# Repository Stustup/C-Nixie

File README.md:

<# CNIX - Nixie Tube Clock ->WORK IN PROGRESS

CNIX is a nixie tube clock which accepts many diffrent nixie tubes with only slight modifications to the tube carrier board. 

The motivation was, that there are not many clocks out there that let you use almost any nixie tube you like. Most have fixed power supplies, 
underdesigned driver stages or inflexible microcontrollers. I hope to tackle these problems with an adjustable boost converter PSU, extremely 
flexible (and electrically protected) driver stages and an open source firmware written with free tools.

## Schematic

The control board consists of 3 parts:
- Power Supply
- Microcontroller
- I/O
- GPIO header for future ideas and feature expansion

Power comes from a simple USB-C plug configured for 5V 3A max with the 5k1 CC line resistors. I thought about adding a PD controller for higher input voltages,
but this would just have added complexity and locked you into more expensive USB PD power supplies.

The µC is a STM32G051, because it has an included RTC *with* added Vbat pin for an external battery, so that the RTC remembers time even when powered off. 
The unused GPIOs are broken out to a connector, so that in the future one could add cool stuff like a radio time reciever, a display or wifi.
Time is set manually with the push buttons on top. 

The PSU is heavily inspired by [this site](https://surfncircuits.com/2018/02/03/optimizing-the-5v-to-170v-nixie-tube-power-supply-design-part-2/). I highly advise you giving it a read. The article goes in depth with boost converter design and its challanges.

## Neat features

### Addon Boards
I designed an addon-board which just plugs into the broken out pins on the control board, to host all kinds of stuff. The one i already made has an DCF77 antenna for automatically getting the exact time OTA in germany. It also holds a HTU21 temperature and humidity sensor from TE, which can be accessed via a single press on the "menu" button on the control board. 
The addon-boards get detected via two pins (D2 a& D3), which form a 2 bit id system. so 0b11 means no board is connected, because i used internal pullups. the DCF77 board has the id 0b00, which deactivates the manual time setting menu and adds the temperature and humidity menu. 
With this all kinds of boards are possible, for example an ESP32 addon board with ESP-Home installed to integrate the clock and a sensor into homeassistant.

On the DCF77 Addon board there is a single pin to give structural strength to a simple perfboard on the main breakout bus. One can use this in tandem with the A1, A2, A3, A4, F0 and F1 pins.

![DCF77 Addon Board]

### Turn on/off timers
You can set power on and off times in the clock natively, so that the nixies dont always glow. With this the HT-power supply also gets deactivated to save power and lifespan of the parts. More advanced features like weekday dependant times have to be programmed directly into the µC, except if you want to code a big menu with just 3 buttons and 2 LEDs.

## TODO

- Change to new MCU. STM32H5 or ESP32. ESP32 for Wifi stuff like syncing time, Homeassistant integration etc. Could be done as module for the pinheader. STM32H5 for USBC pd
    - (DONE) Not necessary, BUT-> Create Plugin board for a DCF77 reciever conencting via GPIO
    - Addon board for Homeassistant Integration?
- (DONE) lower value caps for the LSE
- USB-PD (only with STM32H5) (Not neccessary)
- (DONE) HTU21 Temp and relative humidity sensor

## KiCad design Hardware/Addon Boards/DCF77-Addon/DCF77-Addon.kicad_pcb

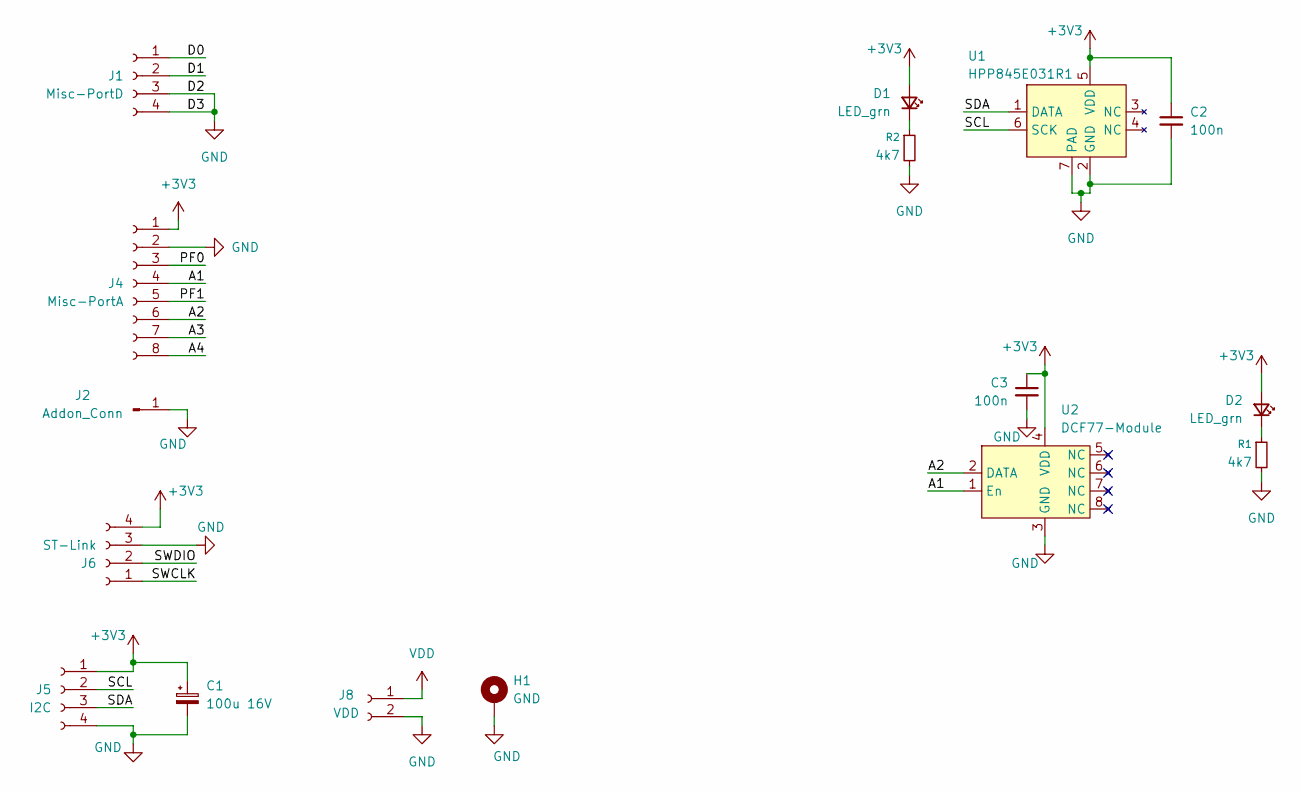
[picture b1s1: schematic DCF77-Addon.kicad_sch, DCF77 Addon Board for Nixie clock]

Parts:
C1: 100u 16V; CP_Elec_6.3x7.7
C2, C3: 100n; C_0805_2012Metric_Pad1.18x1.45mm_HandSolder
D1, D2: LED_grn; LED_0805_2012Metric_Pad1.15x1.40mm_HandSolder
H1: GND; TestPoint_Loop_D3.80mm_Drill2.0mm
J1: Misc-PortD; PinSocket_1x04_P2.54mm_Vertical
J2: Addon_Conn; PinHeader_1x01_P2.54mm_Vertical
J4: Misc-PortA; PinSocket_1x08_P2.54mm_Vertical
J5: I2C; PinSocket_1x04_P2.54mm_Vertical
J6: ST-Link; PinSocket_1x04_P2.54mm_Vertical
J8: VDD; PinSocket_1x02_P2.54mm_Vertical
R1, R2: 4k7; R_0805_2012Metric_Pad1.20x1.40mm_HandSolder
U1: HPP845E031R1; Maxim_TDFN-6-1EP_3x3mm_P0.95mm_EP1.5x2.3mm; Mouser Nr. 824-HPP845E031R1
U2: DCF77-Module

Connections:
+3V3: C1.1, C2.1, C3.1, D1.2 (A), D2.2 (A), J4.1, J5.1, J6.4, U1.5 (VDD), U2.4 (VDD)
/A1: J4.4, U2.1 (En)
/A2: J4.6, U2.2 (DATA)
/A3: J4.7
/A4: J4.8
/D0: J1.1
/D1: J1.2
/PF0: J4.3
/PF1: J4.5
/SCL: J5.2, U1.6 (SCK)
/SDA: J5.3, U1.1 (DATA)
/SWCLK: J6.1
/SWDIO: J6.2
GND: C1.2, C2.2, C3.2, H1.1, J1.3, J1.4, J2.1, J4.2, J5.4, J6.3, J8.2, R1.2, R2.2, U1.2 (GND), U1.7 (PAD), U2.3 (GND)
unnamed: D1.1 (K), R2.1
unnamed: D2.1 (K), R1.1
VDD: J8.1

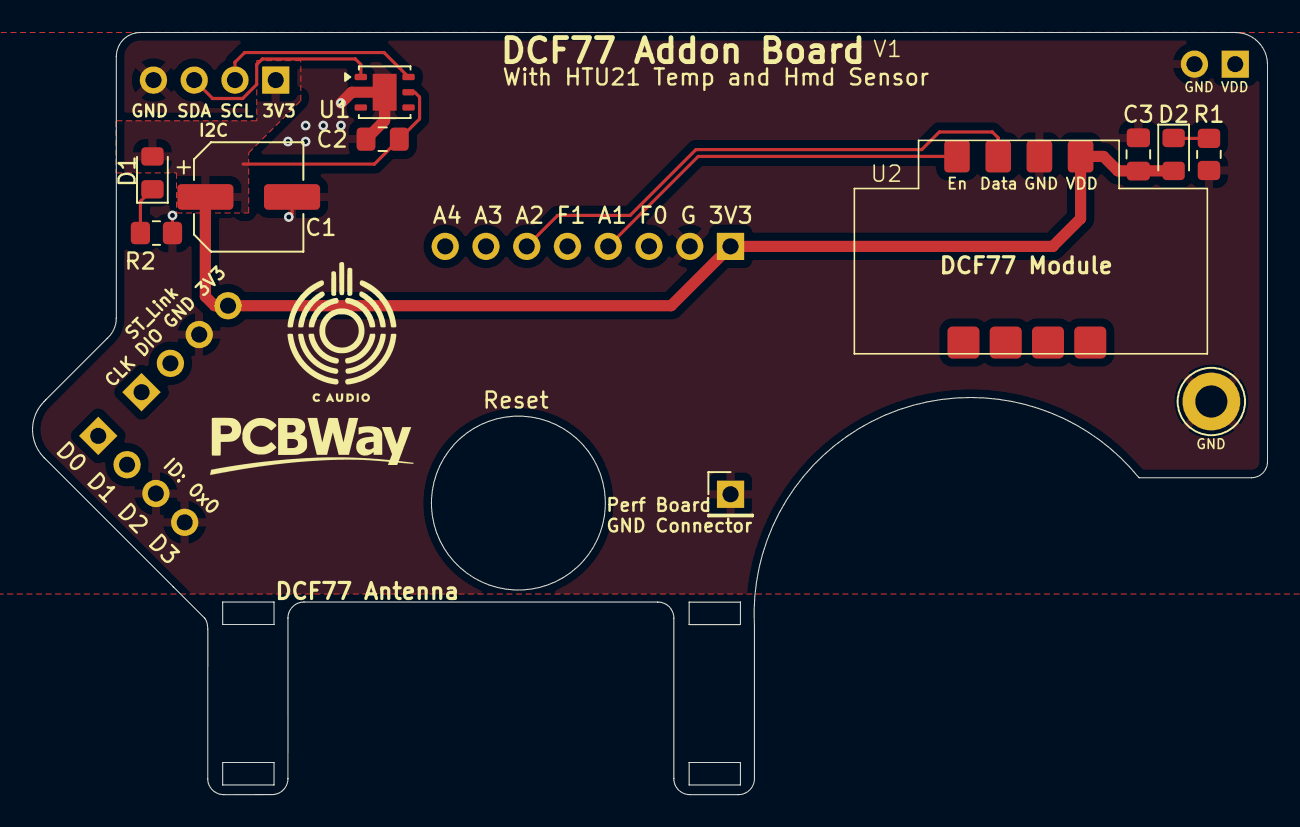
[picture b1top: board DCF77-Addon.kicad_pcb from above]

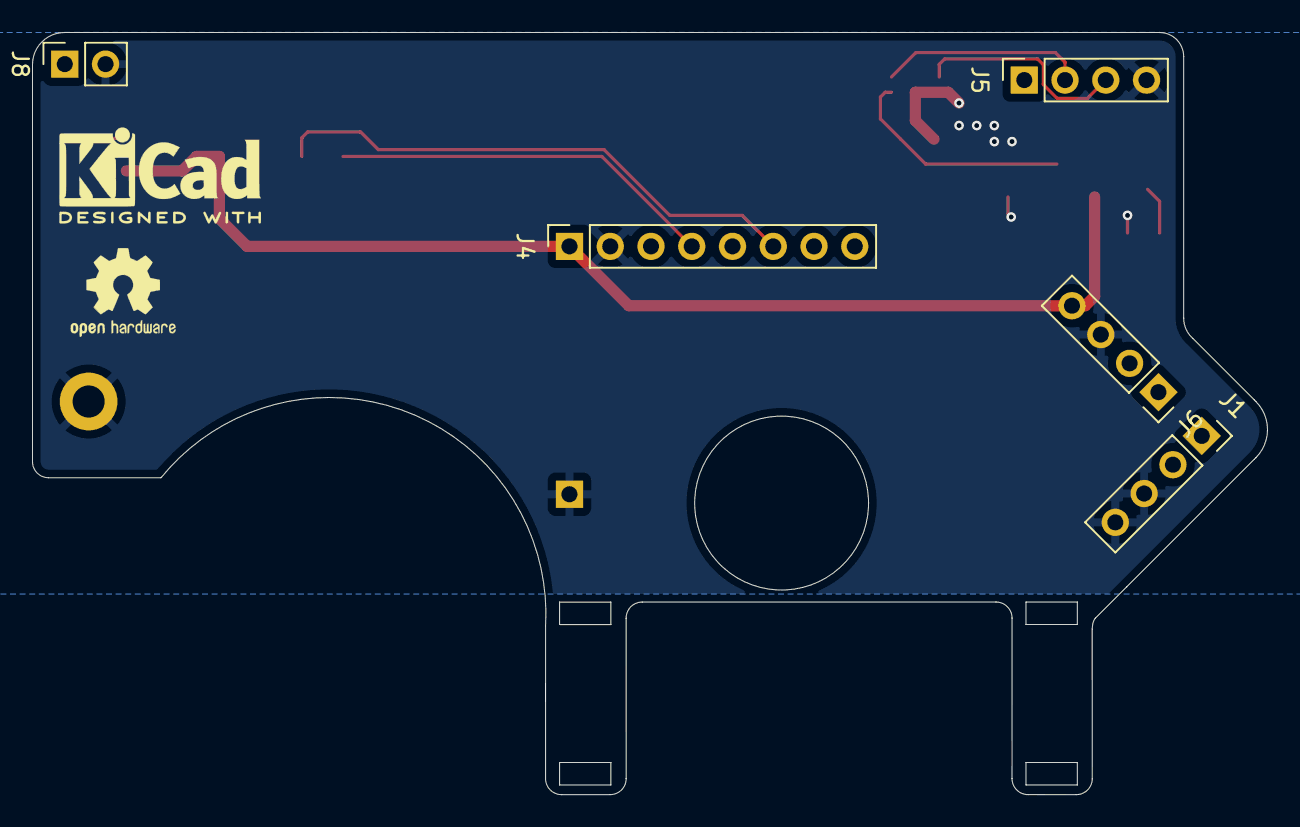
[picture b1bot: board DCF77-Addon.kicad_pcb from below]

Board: 2 copper layers, 77.0 x 47.5 mm, 16 parts (5 on the bottom side), 8 nets.

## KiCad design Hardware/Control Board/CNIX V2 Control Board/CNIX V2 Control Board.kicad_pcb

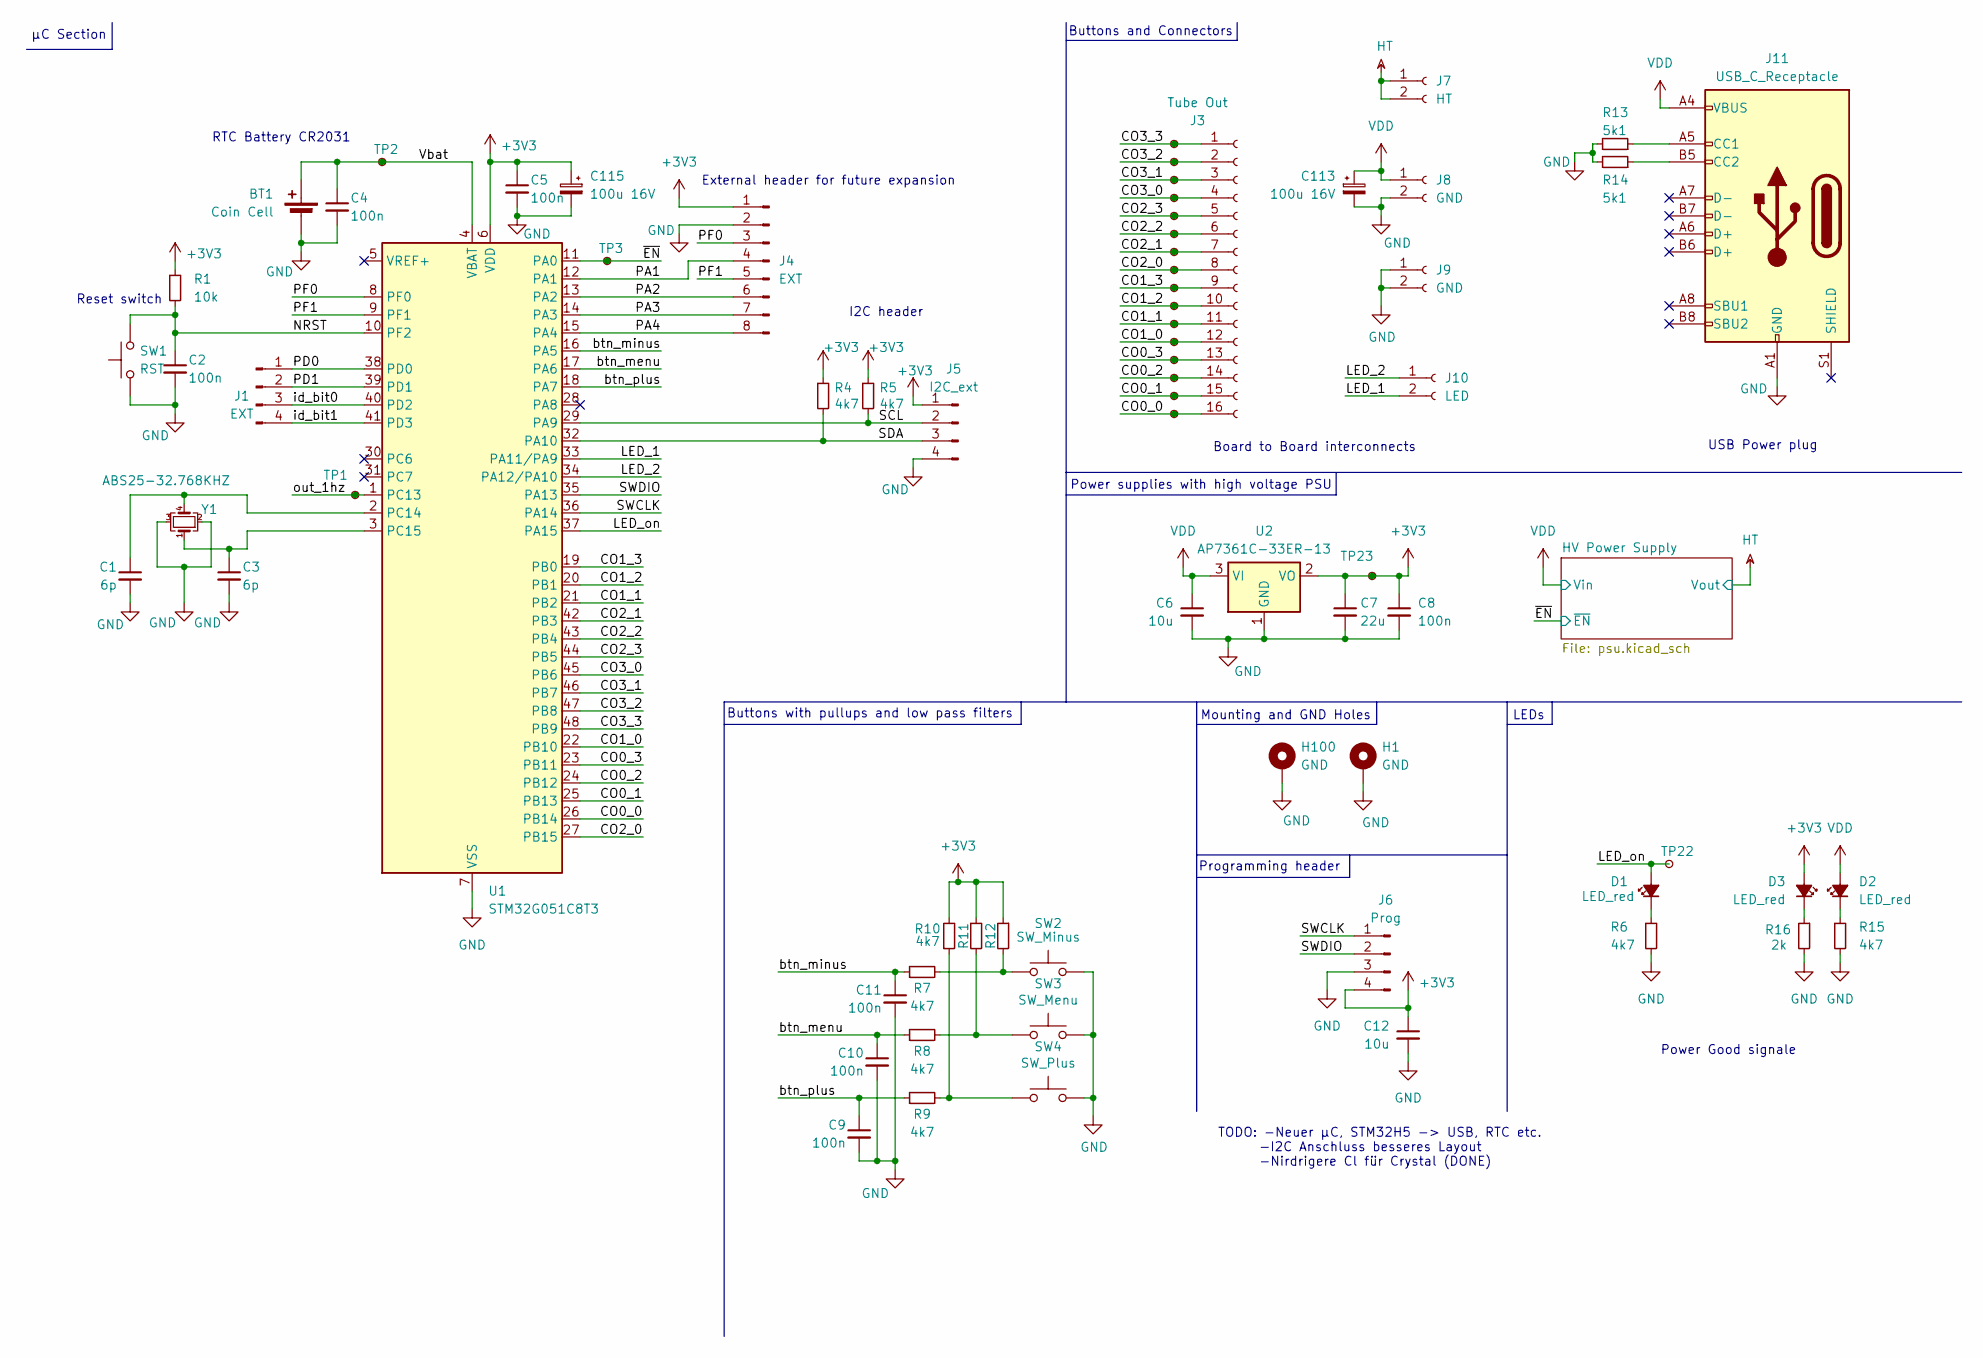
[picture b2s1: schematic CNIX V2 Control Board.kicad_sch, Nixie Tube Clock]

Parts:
BT1: Coin Cell; BatteryHolder_Renata_SMTU2032-LF_1x2032; Mouser Nr. 614-SMTU2032-LF.TR
C1, C3: 6p; C_0805_2012Metric_Pad1.18x1.45mm_HandSolder; Mouser Nr. 80-C0805C180K5HACTU
C2, C4, C5, C8, C9, C10, C11: 100n; C_0805_2012Metric_Pad1.18x1.45mm_HandSolder
C6, C12: 10u; C_0805_2012Metric_Pad1.18x1.45mm_HandSolder; Mouser Nr. 187-CL21B106KPQNNNE
C7: 22u; C_0805_2012Metric_Pad1.18x1.45mm_HandSolder; Mouser Nr. 187-CL21A226MQQNNNG
C113, C115: 100u 16V; CP_Elec_6.3x7.7; Mouser Nr. 710-865080343009
D1, D2, D3: LED_red; LED_0805_2012Metric_Pad1.15x1.40mm_HandSolder
H1: GND; TestPoint_Loop_D3.80mm_Drill2.0mm
H100: GND; TestPoint_Plated_Hole_D3.0mm
J1: EXT; PinHeader_1x04_P2.54mm_Vertical
J3: Tube Out; PinSocket_2x08_P2.54mm_Vertical
J4: EXT; PinHeader_1x08_P2.54mm_Vertical
J5: I2C_ext; PinHeader_1x04_P2.54mm_Vertical
J6: Prog; PinHeader_1x04_P2.54mm_Vertical
J7: HT; PinSocket_1x02_P2.54mm_Vertical
J8, J9: GND; PinSocket_1x02_P2.54mm_Vertical
J10: LED; PinSocket_1x02_P2.54mm_Vertical
J11: USB_C_Receptacle; USB_C_Receptacle_GCT_USB4085
R1: 10k; R_0805_2012Metric_Pad1.20x1.40mm_HandSolder
R4, R5, R6, R7, R8, R9, R10, R11, R12, R15: 4k7; R_0805_2012Metric_Pad1.20x1.40mm_HandSolder; Mouser Nr. 603-RC0805FR-074K7P
R13, R14: 5k1; R_0805_2012Metric_Pad1.20x1.40mm_HandSolder; Mouser Nr. 652-CR0805FX-5101ELF
R16: 2k; R_0805_2012Metric_Pad1.20x1.40mm_HandSolder; Mouser Nr. 603-RC0805FR-132KL
SW1: RST; SW_SPST_Omron_B3FS-100xP
SW2: SW_Minus; SW_Tactile_SPST_Angled_PTS645Vx31-2LFS
SW3: SW_Menu; SW_Tactile_SPST_Angled_PTS645Vx31-2LFS
SW4: SW_Plus; SW_Tactile_SPST_Angled_PTS645Vx31-2LFS
TP1, TP2, TP3, TP22, TP23: TestPoint_Small; TestPoint_Pad_D1.5mm
TP4, TP5, TP6, TP7, TP8, TP9, TP10, TP11, TP12, TP13, TP14, TP15, TP16, TP17, TP18, TP19: TestPoint_Small; TestPoint_THTPad_D1.0mm_Drill0.5mm
U1: STM32G051C8T3; LQFP-48_7x7mm_P0.5mm; Mouser Nr. 511-STM32G051C8T3
U2: AP7361C-33ER-13; SOT-223-3_TabPin2; Mouser-Nr. 621-AP7361C-33ER-13
Y1: ABS25-32.768KHZ; Crystal_SMD_Abracon_ABS25-4Pin_8.0x3.8mm; Mouser Nr. 815-ABS25-32.7-6-1-T

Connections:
+3V3: C5.1, C7.1, C8.1, C12.1, C115.1, D3.2 (A), J4.1, J5.1, J6.4, R1.1, R4.1, R5.1, R10.2, R11.1, R12.1, TP23.1, U1.6 (VDD), U2.2 (VO)
/CO0_0: J3.16, TP19.1, U1.26 (PB14)
/CO0_1: J3.15, TP18.1, U1.25 (PB13)
/CO0_2: J3.14, TP17.1, U1.24 (PB12)
/CO0_3: J3.13, TP16.1, U1.23 (PB11)
/CO1_0: J3.12, TP15.1, U1.22 (PB10)
/CO1_1: J3.11, TP14.1, U1.21 (PB2)
/CO1_2: J3.10, TP13.1, U1.20 (PB1)
/CO1_3: J3.9, TP12.1, U1.19 (PB0)
/CO2_0: J3.8, TP11.1, U1.27 (PB15)
/CO2_1: J3.7, TP10.1, U1.42 (PB3)
/CO2_2: J3.6, TP9.1, U1.43 (PB4)
/CO2_3: J3.5, TP8.1, U1.44 (PB5)
/CO3_0: J3.4, TP7.1, U1.45 (PB6)
/CO3_1: J3.3, TP6.1, U1.46 (PB7)
/CO3_2: J3.2, TP5.1, U1.47 (PB8)
/CO3_3: J3.1, TP4.1, U1.48 (PB9)
/LED_1: J10.2, U1.33 (PA11/PA9)
/LED_2: J10.1, U1.34 (PA12/PA10)
/LED_on: D1.2 (A), TP22.1, U1.37 (PA15)
/NRST: C2.1, R1.2, SW1.2, U1.10 (PF2)
/PA1: J4.4, U1.12 (PA1)
/PA2: J4.6, U1.13 (PA2)
/PA3: J4.7, U1.14 (PA3)
/PA4: J4.8, U1.15 (PA4)
/PD0: J1.1, U1.38 (PD0)
/PD1: J1.2, U1.39 (PD1)
/PF0: J4.3, U1.8 (PF0)
/PF1: J4.5, U1.9 (PF1)
/SCL: J5.2, R5.2, U1.29 (PA9)
/SDA: J5.3, R4.2, U1.32 (PA10)
/SWCLK: J6.1, U1.36 (PA14)
/SWDIO: J6.2, U1.35 (PA13)
/Vbat: BT1.1 (+), C4.1, TP2.1, U1.4 (VBAT)
/btn_menu: C10.1, R8.1, U1.17 (PA6)
/btn_minus: C11.1, R7.1, U1.16 (PA5)
/btn_plus: C9.1, R9.1, U1.18 (PA7)
/id_bit0: J1.3, U1.40 (PD2)
/id_bit1: J1.4, U1.41 (PD3)
/out_1hz: TP1.1, U1.1 (PC13)
/~EN: TP3.1, U1.11 (PA0); also elsewhere on the board
GND: BT1.2 (-), C1.2, C2.2, C3.2, C4.2, C5.2, C6.2, C7.2, C8.2, C9.2, C10.2, C11.2, C12.2, C113.2, C115.2, H1.1, H100.1, J4.2, J5.4, J6.3, J8.2, J9.1, J9.2, J11.A1 (GND), J11.A12 (GND), J11.B1 (GND), J11.B12 (GND), R6.2, R13.2, R14.2, R15.2, R16.2, SW1.1, SW2.2, SW3.2, SW4.2, U1.7 (VSS), U2.1 (GND), Y1.2, Y1.3; also elsewhere on the board
HT: J7.1, J7.2; also elsewhere on the board
unnamed: D1.1 (K), R6.1
unnamed: D2.1 (K), R15.1
unnamed: D3.1 (K), R16.1
unnamed: J11.A5 (CC1), R13.1
unnamed: J11.B5 (CC2), R14.1
unnamed: R9.2, R10.1, SW4.1
unnamed: R8.2, R11.2, SW3.1
unnamed: R7.2, R12.2, SW2.1
unnamed: C1.1, U1.2 (PC14), Y1.4
unnamed: C3.1, U1.3 (PC15), Y1.1
VDD: C6.1, C113.1, D2.2 (A), J8.1, J11.A4 (VBUS), J11.A9 (VBUS), J11.B4 (VBUS), J11.B9 (VBUS), U2.3 (VI); also elsewhere on the board

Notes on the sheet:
Board to Board interconnects
RTC Battery CR2031
µC Section
Programming header
External header for future expansion
Mounting and GND Holes
TODO: -Neuer µC, STM32H5 -> USB, RTC etc. -I2C Anschluss besseres Layout -Nirdrigere Cl für Crystal (DONE)
Power supplies with high voltage PSU
Buttons with pullups and low pass filters
Power Good signale
I2C header
USB Power plug
Reset switch
LEDs
Buttons and Connectors

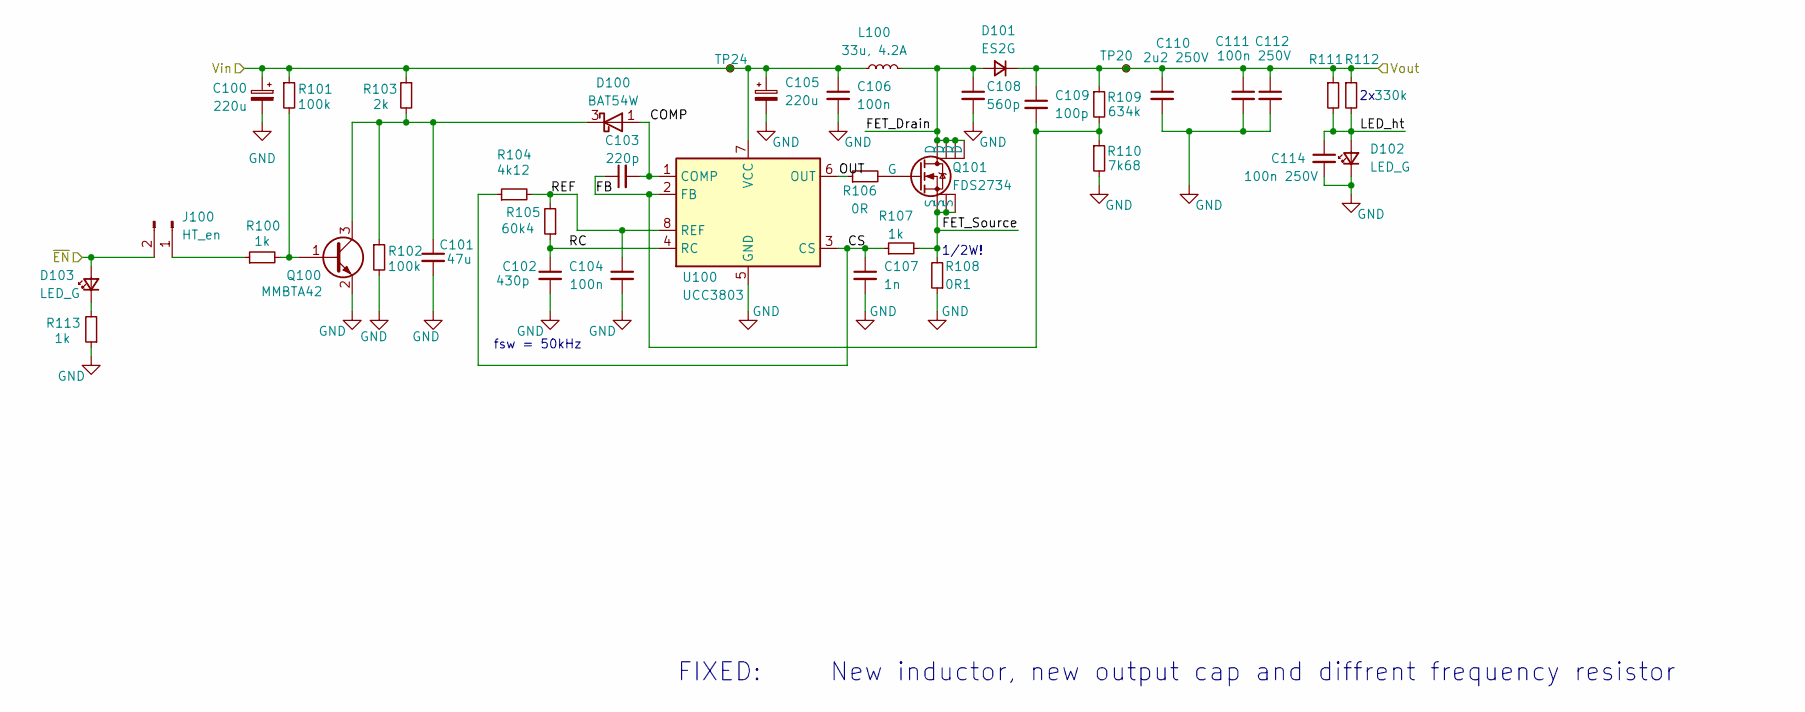
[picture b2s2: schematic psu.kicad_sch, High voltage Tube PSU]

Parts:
C100, C105: 220u; CP_Elec_8x10; Mouser Nr. 647-UUX1E221MNL6GS
C101: 47u; C_0805_2012Metric_Pad1.18x1.45mm_HandSolder; Mouser Nr. 187-CL21A476MRYNNNE
C102: 430p; C_0805_2012Metric_Pad1.18x1.45mm_HandSolder; Mouser Nr. 80-C0805C431J5G
C103: 220p; C_0805_2012Metric_Pad1.18x1.45mm_HandSolder; Mouser Nr. 710-885012207082
C104, C106: 100n; C_0805_2012Metric_Pad1.18x1.45mm_HandSolder
C107: 1n; C_0805_2012Metric_Pad1.18x1.45mm_HandSolder; Mouser Nr. 187-CL21B102KBANNNC
C108: 560p; C_0805_2012Metric_Pad1.18x1.45mm_HandSolder; Mouser Nr. 80-C0805C561K2R
C109: 100p; C_0805_2012Metric_Pad1.18x1.45mm_HandSolder; Mouser Nr. 581-08052C101K
C110: 2u2 250V; C_2220_5750Metric_Pad1.97x5.40mm_HandSolder; Mouser Nr. 710-885342214003
C111: 100nf 250V; C_0805_2012Metric_Pad1.18x1.45mm_HandSolder; Mouser Nr. 810-CGA4J3X7T2E104MA
C112, C114: 100n 250V; C_0805_2012Metric_Pad1.18x1.45mm_HandSolder; Mouser Nr. 810-CGA4J3X7T2E104MA
D100: BAT54W; SOT-323_SC-70; Mouser-Nr. 637-BAT54W
D101: ES2G; D_SMB_Handsoldering; Mouser Nr. 603-ES2G
D102, D103: LED_G; LED_0805_2012Metric
J100: HT_en; PinHeader_1x02_P2.54mm_Vertical
L100: 33u, 4.2A; L_12x12mm_H8mm; Mouser Nr. 7447709330
Q100: MMBTA42; SOT-23
Q101: FDS2734; SO-8_3.9x4.9mm_P1.27mm; Mouser Nr. 512-FDS2734
R100, R107, R113: 1k; R_0805_2012Metric_Pad1.20x1.40mm_HandSolder
R101, R102: 100k; R_0805_2012Metric_Pad1.20x1.40mm_HandSolder
R103: 2k; R_0805_2012Metric_Pad1.20x1.40mm_HandSolder; Mouser Nr. 603-RC0805FR-132KL
R104: 4k12; R_0805_2012Metric_Pad1.20x1.40mm_HandSolder; Mouser Nr. 603-RC0805FR-074K12L
R105: 60k4; R_0805_2012Metric_Pad1.20x1.40mm_HandSolder; Mouser Nr. 603-RE0805FRE0747KL
R106: 0R; R_0805_2012Metric_Pad1.20x1.40mm_HandSolder
R108: 0R1; R_1206_3216Metric_Pad1.30x1.75mm_HandSolder; Mouser Nr. 660-UR73VH2BTTDR100F
R109: 634k; R_1206_3216Metric_Pad1.30x1.75mm_HandSolder; Mouser Nr. 71-CRCW0805634KFKEA
R110: 7k68; R_1206_3216Metric_Pad1.30x1.75mm_HandSolder; Mouser Nr. 603-RC0805FR-077K68L
R111, R112: 330k; R_0805_2012Metric_Pad1.20x1.40mm_HandSolder; Mouser Nr. 603-AC0805FR-07330KL
TP20, TP24: TestPoint_Small; TestPoint_Pad_D1.5mm
U100: UCC3803; SOIC-8_3.9x4.9mm_P1.27mm; Mouser Nr. 595-UCC3803DTR

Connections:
/HV Power Supply/COMP: C103.2, D100.1 (A), U100.1 (COMP)
/HV Power Supply/CS: C107.1, R104.1, R107.1, U100.3 (CS)
/HV Power Supply/FB: C103.1, C109.2, R109.2, R110.1, U100.2 (FB)
/HV Power Supply/FET_Drain: C108.1, D101.2 (A), L100.2, Q101.5 (D), Q101.6 (D), Q101.7 (D), Q101.8 (D)
/HV Power Supply/FET_Source: Q101.1 (S), Q101.2 (S), Q101.3 (S), R107.2, R108.2
/HV Power Supply/LED_ht: C114.1, D102.2 (A), R111.2, R112.2
/HV Power Supply/OUT: R106.1, U100.6 (OUT)
/HV Power Supply/RC: C102.1, R105.1, U100.4 (RC)
/HV Power Supply/REF: C104.1, R104.2, R105.2, U100.8 (REF)
/~EN: D103.2 (A), J100.2; also elsewhere on the board
GND: C100.2, C101.2, C102.2, C104.2, C105.2, C106.2, C107.2, C108.2, C110.2, C111.2, C112.2, C114.2, D102.1 (K), Q100.2 (E), R102.2, R108.1, R110.2, R113.1, U100.5 (GND); also elsewhere on the board
HT: C109.1, C110.1, C111.1, C112.1, D101.1 (K), R109.1, R111.1, R112.1, TP20.1; also elsewhere on the board
unnamed: C101.1, D100.3 (K), Q100.3 (C), R102.1, R103.2
unnamed: D103.1 (K), R113.2
unnamed: J100.1, R100.1
unnamed: Q100.1 (B), R100.2, R101.2
unnamed: Q101.4 (G), R106.2
VDD: C100.1, C105.1, C106.1, L100.1, R101.1, R103.1, TP24.1, U100.7 (VCC); also elsewhere on the board

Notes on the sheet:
FIXED: New inductor, new output cap and diffrent frequency resistor
fsw = 50kHz
1/2W!

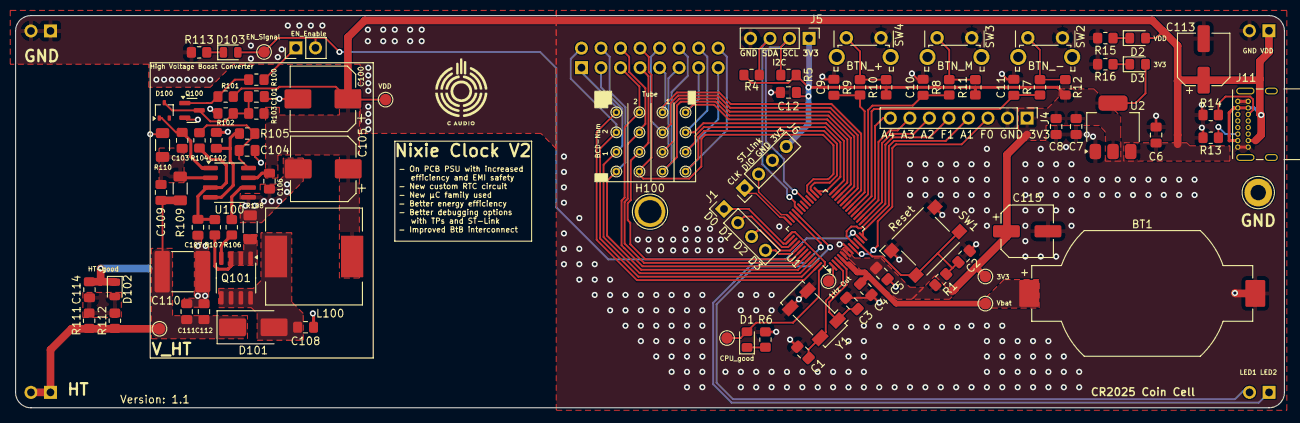
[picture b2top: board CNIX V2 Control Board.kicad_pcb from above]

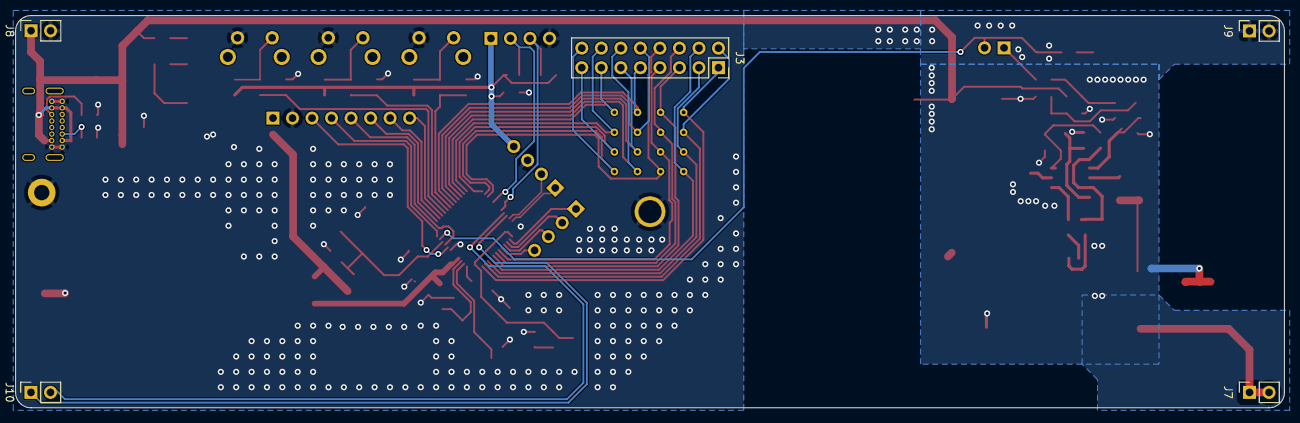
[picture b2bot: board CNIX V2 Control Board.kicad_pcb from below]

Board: 2 copper layers, 165.0 x 51.0 mm, 111 parts (5 on the bottom side), 68 nets.

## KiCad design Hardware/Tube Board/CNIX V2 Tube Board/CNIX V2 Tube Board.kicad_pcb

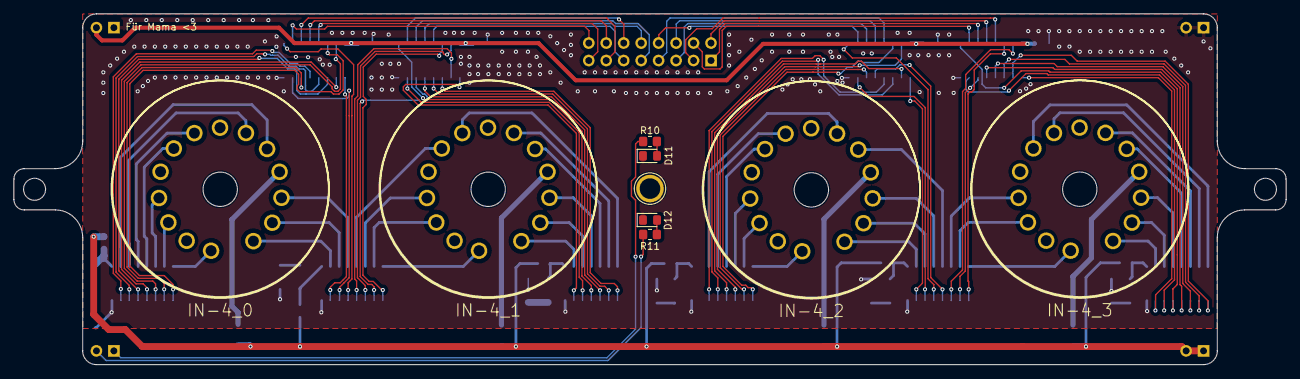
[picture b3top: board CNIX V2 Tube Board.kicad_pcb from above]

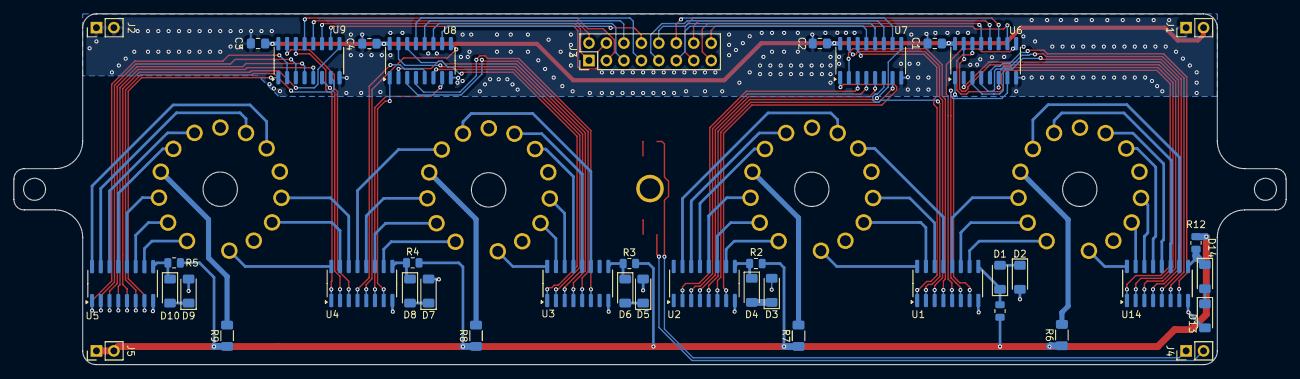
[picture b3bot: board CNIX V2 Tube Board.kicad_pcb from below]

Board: 2 copper layers, 185.0 x 51.0 mm, 50 parts (41 on the bottom side), 119 nets.

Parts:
C1, C2, C3, C4: 100n; C_0805_2012Metric_Pad1.18x1.45mm_HandSolder
D1, D2, D3, D4, D5, D6, D7, D8, D9, D10, D13, D14: TZMC47; D_MiniMELF
D11, D12: LED_Y; LED_0805_2012Metric_Pad1.15x1.40mm_HandSolder
H1: GND; TestPoint_Plated_Hole_D3.0mm
J1: VDD; PinHeader_1x02_P2.54mm_Vertical
J2: GND; PinHeader_1x02_P2.54mm_Vertical
J3: Tube Conn; PinHeader_2x08_P2.54mm_Vertical
J4: LED; PinHeader_1x02_P2.54mm_Vertical
J5: HT; PinHeader_1x02_P2.54mm_Vertical
R1, R2, R3, R4, R5, R12: 47k; R_0805_2012Metric
R6, R7, R8, R9: 18k7; R_1206_3216Metric_Pad1.30x1.75mm_HandSolder
R10, R11: 4k7; R_0805_2012Metric_Pad1.20x1.40mm_HandSolder
U1, U2, U3, U4, U5, U14: SN75468; SOIC-16_3.9x9.9mm_P1.27mm
U6, U7, U8, U9: 4028; SOIC-16_3.9x9.9mm_P1.27mm
U10: IN-4_0; IN-4
U11: IN-4_1; IN-4
U12: IN-4_2; IN-4
U13: IN-4_3; IN-4

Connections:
/CO0_0: J3.16, U6.10 (A)
/CO0_1: J3.15, U6.13 (B)
/CO0_2: J3.14, U6.12 (C)
/CO0_3: J3.13, U6.11 (D)
/CO1_0: J3.12, U7.10 (A)
/CO1_1: J3.11, U7.13 (B)
/CO1_2: J3.10, U7.12 (C)
/CO1_3: J3.9, U7.11 (D)
/CO2_0: J3.8, U8.10 (A)
/CO2_1: J3.7, U8.13 (B)
/CO2_2: J3.6, U8.12 (C)
/CO2_3: J3.5, U8.11 (D)
/CO3_0: J3.4, U9.10 (A)
/CO3_1: J3.3, U9.13 (B)
/CO3_2: J3.2, U9.12 (C)
/CO3_3: J3.1, U9.11 (D)
/LED1: J4.1, R10.1
/LED2: J4.2, R11.1
/T0_D0: U6.3 (S0), U14.5 (I5)
/T0_D1: U6.14 (S1), U14.1 (I1)
/T0_D2: U6.2 (S2), U14.4 (I4)
/T0_D3: U6.15 (S3), U14.3 (I3)
/T0_D4: U1.7 (I7), U6.1 (S4)
/T0_D5: U6.6 (S5), U14.2 (I2)
/T0_D6: U1.6 (I6), U6.7 (S6)
/T0_D7: U6.4 (S7), U14.6 (I6)
/T0_D8: U1.5 (I5), U6.9 (S8)
/T0_D9: U6.5 (S9), U14.7 (I7)
/T0_K0: U10.8 (K0), U14.12 (O5)
/T0_K1: U10.14 (K1), U14.16 (O1)
/T0_K2: U10.9 (K2), U14.13 (O4)
/T0_K3: U10.11 (K3), U14.14 (O3)
/T0_K4: U1.10 (O7), U10.1 (K4)
/T0_K5: U10.12 (K5), U14.15 (O2)
/T0_K6: U1.11 (O6), U10.2 (K6)
/T0_K7: U10.6 (K7), U14.11 (O6)
/T0_K8: U1.12 (O5), U10.3 (K8)
/T0_K9: U10.5 (K9), U14.10 (O7)
/T1_D0: U2.2 (I2), U7.3 (S0)
/T1_D1: U1.1 (I1), U7.14 (S1)
/T1_D2: U1.4 (I4), U7.2 (S2)
/T1_D3: U1.3 (I3), U7.15 (S3)
/T1_D4: U2.7 (I7), U7.1 (S4)
/T1_D5: U1.2 (I2), U7.6 (S5)
/T1_D6: U2.6 (I6), U7.7 (S6)
/T1_D7: U2.3 (I3), U7.4 (S7)
/T1_D8: U2.5 (I5), U7.9 (S8)
/T1_D9: U2.4 (I4), U7.5 (S9)
/T1_K0: U2.15 (O2), U11.8 (K0)
/T1_K1: U1.16 (O1), U11.14 (K1)
/T1_K2: U1.13 (O4), U11.9 (K2)
/T1_K3: U1.14 (O3), U11.11 (K3)
/T1_K4: U2.10 (O7), U11.1 (K4)
/T1_K5: U1.15 (O2), U11.12 (K5)
/T1_K6: U2.11 (O6), U11.2 (K6)
/T1_K7: U2.14 (O3), U11.6 (K7)
/T1_K8: U2.12 (O5), U11.3 (K8)
/T1_K9: U2.13 (O4), U11.5 (K9)
/T2_D0: U3.5 (I5), U8.3 (S0)
/T2_D1: U3.1 (I1), U8.14 (S1)
/T2_D2: U3.4 (I4), U8.2 (S2)
/T2_D3: U3.3 (I3), U8.15 (S3)
/T2_D4: U4.7 (I7), U8.1 (S4)
/T2_D5: U3.2 (I2), U8.6 (S5)
/T2_D6: U4.6 (I6), U8.7 (S6)
/T2_D7: U3.6 (I6), U8.4 (S7)
/T2_D8: U4.5 (I5), U8.9 (S8)
/T2_D9: U4.4 (I4), U8.5 (S9)
/T2_K0: U3.12 (O5), U12.8 (K0)
/T2_K1: U3.16 (O1), U12.14 (K1)
/T2_K2: U3.13 (O4), U12.9 (K2)
/T2_K3: U3.14 (O3), U12.11 (K3)
/T2_K4: U4.10 (O7), U12.1 (K4)
/T2_K5: U3.15 (O2), U12.12 (K5)
/T2_K6: U4.11 (O6), U12.2 (K6)
/T2_K7: U3.11 (O6), U12.6 (K7)
/T2_K8: U4.12 (O5), U12.3 (K8)
/T2_K9: U4.13 (O4), U12.5 (K9)
/T3_D0: U5.2 (I2), U9.3 (S0)
/T3_D1: U4.1 (I1), U9.14 (S1)
/T3_D2: U5.1 (I1), U9.2 (S2)
/T3_D3: U4.3 (I3), U9.15 (S3)
/T3_D4: U5.7 (I7), U9.1 (S4)
/T3_D5: U4.2 (I2), U9.6 (S5)
/T3_D6: U5.6 (I6), U9.7 (S6)
/T3_D7: U5.3 (I3), U9.4 (S7)
/T3_D8: U5.5 (I5), U9.9 (S8)
/T3_D9: U5.4 (I4), U9.5 (S9)
/T3_K0: U5.15 (O2), U13.8 (K0)
/T3_K1: U4.16 (O1), U13.14 (K1)
/T3_K2: U5.16 (O1), U13.9 (K2)
/T3_K3: U4.14 (O3), U13.11 (K3)
/T3_K4: U5.10 (O7), U13.1 (K4)
/T3_K5: U4.15 (O2), U13.12 (K5)
/T3_K6: U5.11 (O6), U13.2 (K6)
/T3_K7: U5.14 (O3), U13.6 (K7)
/T3_K8: U5.12 (O5), U13.3 (K8)
/T3_K9: U5.13 (O4), U13.5 (K9)
GND: C1.2, C2.2, C3.2, C4.2, D2.2 (A), D3.2 (A), D5.2 (A), D7.2 (A), D9.2 (A), D11.1 (K), D12.1 (K), D13.2 (A), H1.1, J1.1, J2.1, J2.2, U1.8 (GND), U2.8 (GND), U3.8 (GND), U4.8 (GND), U5.8 (GND), U6.8 (VSS), U7.8 (VSS), U8.8 (VSS), U9.8 (VSS), U14.8 (GND)
HT: J5.1, J5.2, R1.1, R2.1, R3.1, R4.1, R5.1, R6.1, R7.1, R8.1, R9.1, R12.1
unnamed: D1.2 (A), D2.1 (K)
unnamed: D1.1 (K), R1.2, U1.9 (COM)
unnamed: D3.1 (K), D4.2 (A)
unnamed: D4.1 (K), R2.2, U2.9 (COM)
unnamed: D5.1 (K), D6.2 (A)
unnamed: D6.1 (K), R3.2, U3.9 (COM)
unnamed: D7.1 (K), D8.2 (A)
unnamed: D8.1 (K), R4.2, U4.9 (COM)
unnamed: D9.1 (K), D10.2 (A)
unnamed: D10.1 (K), R5.2, U5.9 (COM)
unnamed: D11.2 (A), R10.2
unnamed: D12.2 (A), R11.2
unnamed: D13.1 (K), D14.2 (A)
unnamed: D14.1 (K), R12.2, U14.9 (COM)
unnamed: R6.2, U10.4 (S)
unnamed: R7.2, U11.4 (S)
unnamed: R8.2, U12.4 (S)
unnamed: R9.2, U13.4 (S)
VDD: C1.1, C2.1, C3.1, C4.1, J1.2, U6.16 (VDD), U7.16 (VDD), U8.16 (VDD), U9.16 (VDD)

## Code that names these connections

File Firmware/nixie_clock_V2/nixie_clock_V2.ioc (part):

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Mcu.Name=STM32G051C(6-8)Tx
Mcu.Package=LQFP48
Mcu.UserName=STM32G051C8Tx
PA0.GPIOParameters=PinState,GPIO_PuPd,GPIO_Label
PA0.GPIO_Label=ht_EN
PA0.GPIO_PuPd=GPIO_PULLUP
PA0.PinState=GPIO_PIN_SET
PA0.Signal=GPIO_Output
PA1.GPIOParameters=GPIO_PuPd,GPIO_Label
PA1.GPIO_Label=dht22_pin
PA1.GPIO_PuPd=GPIO_PULLUP
PA1.Signal=GPIO_Input
PA10.Mode=I2C
PA10.Signal=I2C1_SDA
PA11\ [PA9].GPIOParameters=GPIO_Label
PA11\ [PA9].GPIO_Label=led_sig_bot
PA11\ [PA9].Signal=GPIO_Output
PA12\ [PA10].GPIOParameters=GPIO_Label
PA12\ [PA10].GPIO_Label=led_sig_top
PA12\ [PA10].Signal=GPIO_Output
PA15.GPIOParameters=PinState,GPIO_Label
PA15.GPIO_Label=pwr_led
PA15.PinState=GPIO_PIN_SET
PA15.Signal=GPIO_Output
PA5.GPIOParameters=GPIO_Label,GPIO_ModeDefaultEXTI
PA5.GPIO_Label=btn_minus
PA5.GPIO_ModeDefaultEXTI=GPIO_MODE_IT_FALLING
PA5.Signal=GPXTI5
PA6.GPIOParameters=GPIO_Label,GPIO_ModeDefaultEXTI
PA6.GPIO_Label=btn_menu
PA6.GPIO_ModeDefaultEXTI=GPIO_MODE_IT_FALLING
PA6.Signal=GPXTI6
PA7.GPIOParameters=GPIO_Label,GPIO_ModeDefaultEXTI
PA7.GPIO_Label=btn_plus
PA7.GPIO_ModeDefaultEXTI=GPIO_MODE_IT_FALLING
PA7.Signal=GPXTI7
PA9.Mode=I2C
PA9.Signal=I2C1_SCL
PB0.GPIOParameters=GPIO_Speed,PinState,GPIO_PuPd,GPIO_Label,GPIO_ModeDefaultOutputPP
PB0.GPIO_Label=co1_3
PB0.GPIO_ModeDefaultOutputPP=GPIO_MODE_OUTPUT_PP
PB0.GPIO_PuPd=GPIO_PULLDOWN
PB0.GPIO_Speed=GPIO_SPEED_FREQ_LOW
PB0.PinState=GPIO_PIN_RESET
PB0.Signal=GPIO_Output
PB1.GPIOParameters=GPIO_Speed,PinState,GPIO_PuPd,GPIO_Label,GPIO_ModeDefaultOutputPP
PB1.GPIO_Label=co1_2
PB1.GPIO_ModeDefaultOutputPP=GPIO_MODE_OUTPUT_PP
PB1.GPIO_PuPd=GPIO_PULLDOWN
PB1.GPIO_Speed=GPIO_SPEED_FREQ_LOW
PB1.PinState=GPIO_PIN_RESET
PB1.Signal=GPIO_Output
PB10.GPIOParameters=GPIO_Speed,PinState,GPIO_PuPd,GPIO_Label,GPIO_ModeDefaultOutputPP
PB10.GPIO_Label=co1_0
PB10.GPIO_ModeDefaultOutputPP=GPIO_MODE_OUTPUT_PP
PB10.GPIO_PuPd=GPIO_PULLDOWN
PB10.GPIO_Speed=GPIO_SPEED_FREQ_LOW
PB10.PinState=GPIO_PIN_RESET
PB10.Signal=GPIO_Output
PB11.GPIOParameters=GPIO_Speed,PinState,GPIO_PuPd,GPIO_Label,GPIO_ModeDefaultOutputPP
PB11.GPIO_Label=co0_3
PB11.GPIO_ModeDefaultOutputPP=GPIO_MODE_OUTPUT_PP
PB11.GPIO_PuPd=GPIO_PULLDOWN
PB11.GPIO_Speed=GPIO_SPEED_FREQ_LOW
PB11.PinState=GPIO_PIN_RESET
PB11.Signal=GPIO_Output
PB12.GPIOParameters=GPIO_Speed,PinState,GPIO_PuPd,GPIO_Label,GPIO_ModeDefaultOutputPP
PB12.GPIO_Label=co0_2
PB12.GPIO_ModeDefaultOutputPP=GPIO_MODE_OUTPUT_PP
PB12.GPIO_PuPd=GPIO_PULLDOWN
PB12.GPIO_Speed=GPIO_SPEED_FREQ_LOW
PB12.PinState=GPIO_PIN_RESET
PB12.Signal=GPIO_Output
PB13.GPIOParameters=GPIO_Speed,PinState,GPIO_PuPd,GPIO_Label,GPIO_ModeDefaultOutputPP
PB13.GPIO_Label=co0_1
PB13.GPIO_ModeDefaultOutputPP=GPIO_MODE_OUTPUT_PP
PB13.GPIO_PuPd=GPIO_PULLDOWN
PB13.GPIO_Speed=GPIO_SPEED_FREQ_LOW
PB13.PinState=GPIO_PIN_RESET
PB13.Signal=GPIO_Output
PB14.GPIOParameters=GPIO_Speed,PinState,GPIO_PuPd,GPIO_Label,GPIO_ModeDefaultOutputPP
PB14.GPIO_Label=co0_0
PB14.GPIO_ModeDefaultOutputPP=GPIO_MODE_OUTPUT_PP
PB14.GPIO_PuPd=GPIO_PULLDOWN
PB14.GPIO_Speed=GPIO_SPEED_FREQ_LOW
PB14.PinState=GPIO_PIN_RESET
PB14.Signal=GPIO_Output
PB15.GPIOParameters=GPIO_Speed,PinState,GPIO_PuPd,GPIO_Label,GPIO_ModeDefaultOutputPP
PB15.GPIO_Label=co2_0
PB15.GPIO_ModeDefaultOutputPP=GPIO_MODE_OUTPUT_PP
PB15.GPIO_PuPd=GPIO_PULLDOWN
PB15.GPIO_Speed=GPIO_SPEED_FREQ_LOW
PB15.PinState=GPIO_PIN_RESET
PB15.Signal=GPIO_Output
PB2.GPIOParameters=GPIO_Speed,PinState,GPIO_PuPd,GPIO_Label,GPIO_ModeDefaultOutputPP
PB2.GPIO_Label=co1_1
PB2.GPIO_ModeDefaultOutputPP=GPIO_MODE_OUTPUT_PP
PB2.GPIO_PuPd=GPIO_PULLDOWN
PB2.GPIO_Speed=GPIO_SPEED_FREQ_LOW
PB2.PinState=GPIO_PIN_RESET
PB2.Signal=GPIO_Output
PB3.GPIOParameters=GPIO_Speed,PinState,GPIO_PuPd,GPIO_Label,GPIO_ModeDefaultOutputPP
PB3.GPIO_Label=co2_1
PB3.GPIO_ModeDefaultOutputPP=GPIO_MODE_OUTPUT_PP
PB3.GPIO_PuPd=GPIO_PULLDOWN
PB3.GPIO_Speed=GPIO_SPEED_FREQ_LOW
PB3.PinState=GPIO_PIN_RESET
PB3.Signal=GPIO_Output
PB4.GPIOParameters=GPIO_Speed,PinState,GPIO_PuPd,GPIO_Label,GPIO_ModeDefaultOutputPP
PB4.GPIO_Label=co2_2
PB4.GPIO_ModeDefaultOutputPP=GPIO_MODE_OUTPUT_PP
PB4.GPIO_PuPd=GPIO_PULLDOWN
PB4.GPIO_Speed=GPIO_SPEED_FREQ_LOW
PB4.PinState=GPIO_PIN_RESET
PB4.Signal=GPIO_Output
PB5.GPIOParameters=GPIO_Speed,PinState,GPIO_PuPd,GPIO_Label,GPIO_ModeDefaultOutputPP
PB5.GPIO_Label=co2_3
PB5.GPIO_ModeDefaultOutputPP=GPIO_MODE_OUTPUT_PP
PB5.GPIO_PuPd=GPIO_PULLDOWN
PB5.GPIO_Speed=GPIO_SPEED_FREQ_LOW
PB5.PinState=GPIO_PIN_RESET
PB5.Signal=GPIO_Output
PB6.GPIOParameters=GPIO_Speed,PinState,GPIO_PuPd,GPIO_Label,GPIO_ModeDefaultOutputPP
PB6.GPIO_Label=co3_0
PB6.GPIO_ModeDefaultOutputPP=GPIO_MODE_OUTPUT_PP
PB6.GPIO_PuPd=GPIO_PULLDOWN
PB6.GPIO_Speed=GPIO_SPEED_FREQ_LOW
PB6.PinState=GPIO_PIN_RESET
PB6.Signal=GPIO_Output
PB7.GPIOParameters=GPIO_Speed,PinState,GPIO_PuPd,GPIO_Label,GPIO_ModeDefaultOutputPP
PB7.GPIO_Label=co3_1
PB7.GPIO_ModeDefaultOutputPP=GPIO_MODE_OUTPUT_PP
PB7.GPIO_PuPd=GPIO_PULLDOWN
PB7.GPIO_Speed=GPIO_SPEED_FREQ_LOW
PB7.PinState=GPIO_PIN_RESET
PB7.Signal=GPIO_Output
PB8.GPIOParameters=GPIO_Speed,PinState,GPIO_PuPd,GPIO_Label,GPIO_ModeDefaultOutputPP
PB8.GPIO_Label=co3_2
PB8.GPIO_ModeDefaultOutputPP=GPIO_MODE_OUTPUT_PP
PB8.GPIO_PuPd=GPIO_PULLDOWN
PB8.GPIO_Speed=GPIO_SPEED_FREQ_LOW
PB8.PinState=GPIO_PIN_RESET
PB8.Signal=GPIO_Output
PB9.GPIOParameters=GPIO_Speed,PinState,GPIO_PuPd,GPIO_Label,GPIO_ModeDefaultOutputPP
PB9.GPIO_Label=co3_3
PB9.GPIO_ModeDefaultOutputPP=GPIO_MODE_OUTPUT_PP
PB9.GPIO_PuPd=GPIO_PULLDOWN
PB9.GPIO_Speed=GPIO_SPEED_FREQ_LOW
PB9.PinState=GPIO_PIN_RESET
PB9.Signal=GPIO_Output
PC13.Mode=Calibration_1Hz
PC13.Signal=RTC_OUT1
PC14-OSC32_IN\ (PC14).Mode=LSE-External-Oscillator
PC14-OSC32_IN\ (PC14).Signal=RCC_OSC32_IN
PC15-OSC32_OUT\ (PC15).Mode=LSE-External-Oscillator
PC15-OSC32_OUT\ (PC15).Signal=RCC_OSC32_OUT
PD2.GPIOParameters=GPIO_PuPd,GPIO_Label
PD2.GPIO_Label=id_bit0
PD2.GPIO_PuPd=GPIO_PULLUP
PD2.Signal=GPIO_Input
PD3.GPIOParameters=GPIO_PuPd,GPIO_Label
PD3.GPIO_Label=id_bit1
PD3.GPIO_PuPd=GPIO_PULLUP
PD3.Signal=GPIO_Input
RCC.HSE_VALUE=8000000
RCC.SYSCLKFreq_VALUE=64000000
RCC.SYSCLKSource=RCC_SYSCLKSOURCE_PLLCLK
board=custom

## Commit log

2025-03-11 added readme
2025-03-12 added bom and mouser nr
2025-03-25 added combined 3d model
2025-04-02 added interactive BOM
2025-04-04 Added TODOs and changed cap values for the LSE
2025-12-09 added link to original psu
2026-01-09 pre tube board fix
2026-01-09 finished wiring fix for the tube board
2026-01-12 finished tube PCB IN4 Version
2026-01-12 finished production files
2026-01-12 added gitignore
2026-01-13 control board version 2.1.1 bump and added changelog
2026-01-13 Version bump 2.2.0 -> new regulator and id system
2026-01-13 firmware update: blink timer and interrupt implemented; cleaned up main
2026-01-14 updated firmware: implemented DHT22 sensor, addon board id check, menu structure, led blink display
2026-01-14 control board: added ht-psu enable jumper
2026-01-15 Readme update
    Removed the "do not build" warning because i fixed it. Also showcased some features.
2026-01-24 added silkscreen and updated gerbers
2026-03-10 Enhance PSU section with article recommendation
    Added recommendation to read the PSU design article for more insights.
2026-03-16 Finished design
2026-03-16 finalized design
2026-03-16 finalized DCF77 board and updated 3D pictures
2026-03-16 finalized V2 and cleaned up Silkscreen
2026-03-16 finalized README
2026-03-26 finalized addon board and produced fabrication outputs
